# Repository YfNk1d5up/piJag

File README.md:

# piJag

Audio/Video Screen Unit of Jaguar X Type X400 based on a raspberry and openAuto pro: bluetooth, CarPlay, OBD, remote start, climate module control

[github] https://github.com/YfNk1d5up/piJag

## Hardware & Software

 - This project was initially thought for Jaguar X-Type X400 (2001) but some parts will work for other cars
 - It uses :
    - [Rpi 4B 4GB RAM](https://www.raspberrypi.com/products/raspberry-pi-4-model-b/)
    - [OpenAuto Pro](https://bluewavestudio.io/shop/openauto-pro-car-head-unit-solution/)
    - [CarPiHat](https://thepihut.com/products/carpihat-car-interface-hat-for-raspberry-pi)
    - [10.1" TouchScreen](https://www.amazon.fr/gp/product/B0B4VMNB42/ref=ppx_yo_dt_b_search_asin_image?ie=UTF8&psc=1)
    - [Carlinkit](https://www.amazon.fr/gp/product/B09ZQF182F/ref=ppx_yo_dt_b_asin_title_o05_s00?ie=UTF8&psc=1)
    - [USB Sound Card](https://www.amazon.fr/gp/product/B00IRVQ0F8/ref=ppx_yo_dt_b_asin_title_o04_s00?ie=UTF8&psc=1)
    - [Rear Camera](https://www.amazon.fr/gp/product/B0BG5M8H76/ref=ppx_yo_dt_b_asin_title_o01_s01?ie=UTF8&psc=1)
    - [CVBS to USB adapter](https://www.amazon.fr/gp/product/B0BYJ2892S/ref=ppx_yo_dt_b_asin_title_o01_s00?ie=UTF8&psc=1)
    - [12V Voltage Regulator](https://www.amazon.fr/gp/product/B09Q1XXM6G/ref=ppx_yo_dt_b_asin_title_o02_s00?ie=UTF8&psc=1)
    - [Powered USB Hub](https://www.amazon.fr/gp/product/B0BDFG1WZ7/ref=ppx_yo_dt_b_asin_title_o06_s00?ie=UTF8&psc=1)
    - [ELM327 OBD USB](https://www.amazon.fr/gp/product/B07NSPLVYW/ref=ppx_yo_dt_b_asin_title_o07_s00?ie=UTF8&psc=1)
    - 12V relays, Fan, Microphone, 4Channel Amplificator, HDMI & RCA cables, Audio Splitter ...
 - A custom PCB to control the Climate Control Module with an arduino nano (Kicad & JLCPCB)

## Features

- **Phone** : CarPlay, Android Auto, bluetooth, messages and calls
- **Rear Camera** : Automatic on reverse gear or anytime manually
- **Videos** : Kodi & Youtube
- **OBD** : CAN & SCP (Ford Protocol) messages and control
- **Climate** : Climate Control Module App
- **Mobile App** : Start the car, turn on heater or climatisation from Phone

## Screenshots

Setup not clean for now (you can see the Climate Control Module annoying me for now, explaination later)...

## Integration

### Raspberry Pi and carPiHat

The issue with installing custom hardware on a car is mainly how to power and connect them. Should I use the permanent 12V, switched 12V on key, interior lights 12V ...
The raspberry pi 4B is a 5V small computer that can draw 3A when loads are connected to it.
In this setup, a lot of usb devices are connected and I should consider this ~3A as a constant.
5V 3A, drawn from the car battery makes it impossible keeping powered on the constant battery supply.
In deed it needs to be powered off when I'm not in the car, and it needs a 12V to 5V step-down.
This is where I found [carPiHat](https://github.com/gecko242/CarPiHat) from TJD that saved me a lot of work :
- 12V - 5V buck converter to power the pi and touchscreen, with fuse and filtering.
- Safe shutdown circuitry to allow the pi to control its own power.
-  < 1mA current draw when switched off.
- Dedicated reverse, illumination and aux inputs, all opto isolated.
- 2 opto isolated general purpose inputs. (for a total of 5 inputs)
- 2 high current, high side switched 12V outputs (@1A). (for switching relays, lights ect)
- 1 independent CAN bus port.
- Real time clock to maintain system time across reboots.
- Broken out I2C bus.
- Broken out 1W for temperature sensor ect.
- 5V Power Output for display ect.

So the power aspect is done using this hat for the raspberry, connecting constant 12V, switched 12V, reverse gear input, illumination input, and GND

Then, a script makes the automation of the RPi power off 30s after turning the car off :

```python
import RPi.GPIO as GPIO # import our GPIO module
import time
from subprocess import call

GPIO.setmode(GPIO.BCM) # we are using BCM pin numbering

IGN_PIN = 12		# our 12V switched pin is BCM12
EN_POWER_PIN = 25	# our latch pin is BCM25

ILL_PIN = 13		# our 12V Illumination input pin is BCM13
REVERSE_PIN = 7	# our 12V Reverse Gear input pin is BCM7

IGN_LOW_TIME = 30 # time (s) before a shutdown is initiated after power loss

GPIO.setup(IGN_PIN, GPIO.IN) # set our 12V switched pin as an input
GPIO.setup(ILL_PIN, GPIO.IN) # same for ill and reverse 
GPIO.setup(REVERSE_PIN, GPIO.IN)

GPIO.setup(EN_POWER_PIN, GPIO.OUT, initial=GPIO.HIGH) # set our latch as an output

GPIO.output(EN_POWER_PIN, 1) # latch our power. We are now in charge of switching power off

ignLowCounter = 0

while 1:
	if GPIO.input(IGN_PIN) != 1: 				# if our 12V switched is not disabled
		time.sleep(1)							# wait a second
		ignLowCounter += 1						# increment our counter
		if ignLowCounter > IGN_LOW_TIME:		# if it has been switched off for >10s
			print("Shutting Down")
			call("sudo shutdown -h now", shell=True)	# tell the Pi to shut down
	else:
		ignLowCounter = 0 						# reset our counter, 12V switched is HIGH again

        time.sleep(0.1)  # Add a small sleep delay to reduce CPU usage
```

As said in TJD documentation in the *Opto-Isolated Inputs* section, I needed to redirect the CS1 pin to BCM24 to get ill and reverse inputs to work.

From the hat I also used the 2 outputs to control relays :
- One relay powers the **4Channels Audio Amplifier remote** and the rear camera with 12V
- The other powers the **36W USB Hub** to relieve the strain on the raspberry and charge devices.

(picture)

#### **Parts to come with carPiHat** :
- CAN integration
- I/O expander to add remote powering the car and other stuff

### TouchScreen 

Simply an HDMI and touch USB connected to the RPi, plus 5V power coming from the carPiHat

### Suffering from Hot Temperatures

During summer 2023, a lot of heat has made the setup suffer. This is where I add a 12V computer power fan to help keeping the whole setup at acceptable temperatures.

## obdSniffer

To add more control on the car, I tried to hack bus networks through the OBD2 port.

### CAN Bus

Following this awesome serie from Youtube [How to hack your car ](https://youtu.be/cAAzXM5vsi0) by Adam Varga and using his python&Qt [CAN_Gui](https://github.com/adamtheone/canDrive), I copy the setup to hack into my CAN Bus.

Here are for example some data I decoded : 

### SCP Bus

As the X-Type shares its creation with the Ford Mondeo, the car uses SAEJ1850 PWM aka **Standard Corporate Protocol** or **SCP** to communicate low priority information between modules.

A modification of Adam Varga code brings me the SCP decoding using the **ELM327 OBD2 USB Reader** using **AT** commands.
Modified functions :
*serialPacketReceiverCallback*
*serialPortConnect*
file *SerialReader.py*

(You can see some SCP data on the previous screenshot)

To achieve that, first I did some tests using AT on linux terminal

```bash
sudo screen /dev/ttyUSB0 38400
```

```bash
>atz
ELM327 v1.5

>atl1
OK

>ath1
OK

>ats1
OK

>atal
OK

>atsp1
OK

>atma

```

For AT commands explanation, SCP application case and another hardware setup, see this thread : https://www.jaguarforum.com/threads/reverse-engineering-hacking-scp-bus-to-xj-x350-x358-s-type-and-x-type.108639/

Example output :

```bash
81 29 60 02 0081 29 60 02 00 00 11
41 87 60 04 08 B1
81 7B 60 02 00 4C
81 7B 60 02 00 4C
```

See [X-Type Electrical Guide CAN/SCP](https://github.com/YfNk1d5up/piJag/blob/cf38571dc9505988becb3cf82d76548922db3a51/Docs/JagClimModule.pdf) to find more information about CAN and SCP messages

## OpenAuto Pro setup

## Climate Control Module Hack

The goal here was to remove the Control Unit that is space-consuming and overall avoid me to install the screen properly without destroying the case.
To continue adding a modern touch to my X-Type, I enjoy controlling the climate directly on the touchscreen via an app on openAuto Pro.

Firstly, I need to understand well how the existing module works.
So I bought another one to avoid getting stuck breaking it : in deed, it is connected to the CAN Bus and the car will not start if the module doesn't work or isn't connected to the bus.

By the CAN and SCP analyse done previously, I found that buttons user actions are not going through any bus on the car, plus the electrical documentation shows that the module only communicate with other modules to say an action has been performed.
FYI, the second X-Type (X404) added LIN to the buses, where climate, windows control, driver wheel buttons, etc, communicate through it.

But no chance, that is not the case for my version. So sending commands on buses to control the climate module is impossible.

That said, there is no other way than hacking electronics of the module by adding a custom Mod PCB.

The Module consists in 2 PCBs connected by a 20 wires ribbon. On the electrical documentation, only the global module connections to the rest of the car is detailed. 
Lucky for me, somebody already took a look into that module, because he wanted to change the screen to a modern one. The report is joined in [David's initial HVAC Sniffer](https://github.com/YfNk1d5up/piJag/blob/cf38571dc9505988becb3cf82d76548922db3a51/Docs/p10018_jag_hvac_sniffer.zip)

The first PCB contains the MCU which does CAN communication to the rest of the vehicule, control of fans, compressor, etc : that is the one I want to keep.
The second one contains all the buttons, the LCD screen, a digital encoder, and maybe a second propietary MCU impossible to identify : I want to replace this PCB.
Doing some retro-engineering and finding the documentation of the MCU in the first PCB, here is the connection from and to that second PCB :

[Initial retro-engineering of the 2nd PCB](https://github.com/YfNk1d5up/piJag/blob/cf38571dc9505988becb3cf82d76548922db3a51/Docs/piJagClim_existing_module.pdf)

You can see here a switches matrix, using 6 wires for 12 buttons. An I2C screen connected straigth to the main MCU, a rotary encoder also directly connected to the main board.
What I used for the buttons is analog switches, that works as relays except that they are small 14 pins chips, which each entry is controlled by an Arduino digital pin. For the rotary encoder, an Arduino Nano can easily simulate the signals by using two digital pins.
Finally, using David's work about the i2c screen, I can get the information coming from the main MCU by decoding it using A4 and A5 pins on the Nano.

And so here is the mod board :

JLCPCB Manufacture :

![PCB not mounted]
![PCB mounted]

To communicate with the arduino onboard, a pyQt App controls the mod, associated with an arduino code that simulates the action and transmit the i2c data.

[pyQtApp](Software/piJagClimApp)
[piJagClimI2C.ino](Hardware/piJagClim/newPCB/arduino/piJagClimI2C/piJagClimI2C.ino)

Here you can see the Qt App v0.1 :

## Ressources

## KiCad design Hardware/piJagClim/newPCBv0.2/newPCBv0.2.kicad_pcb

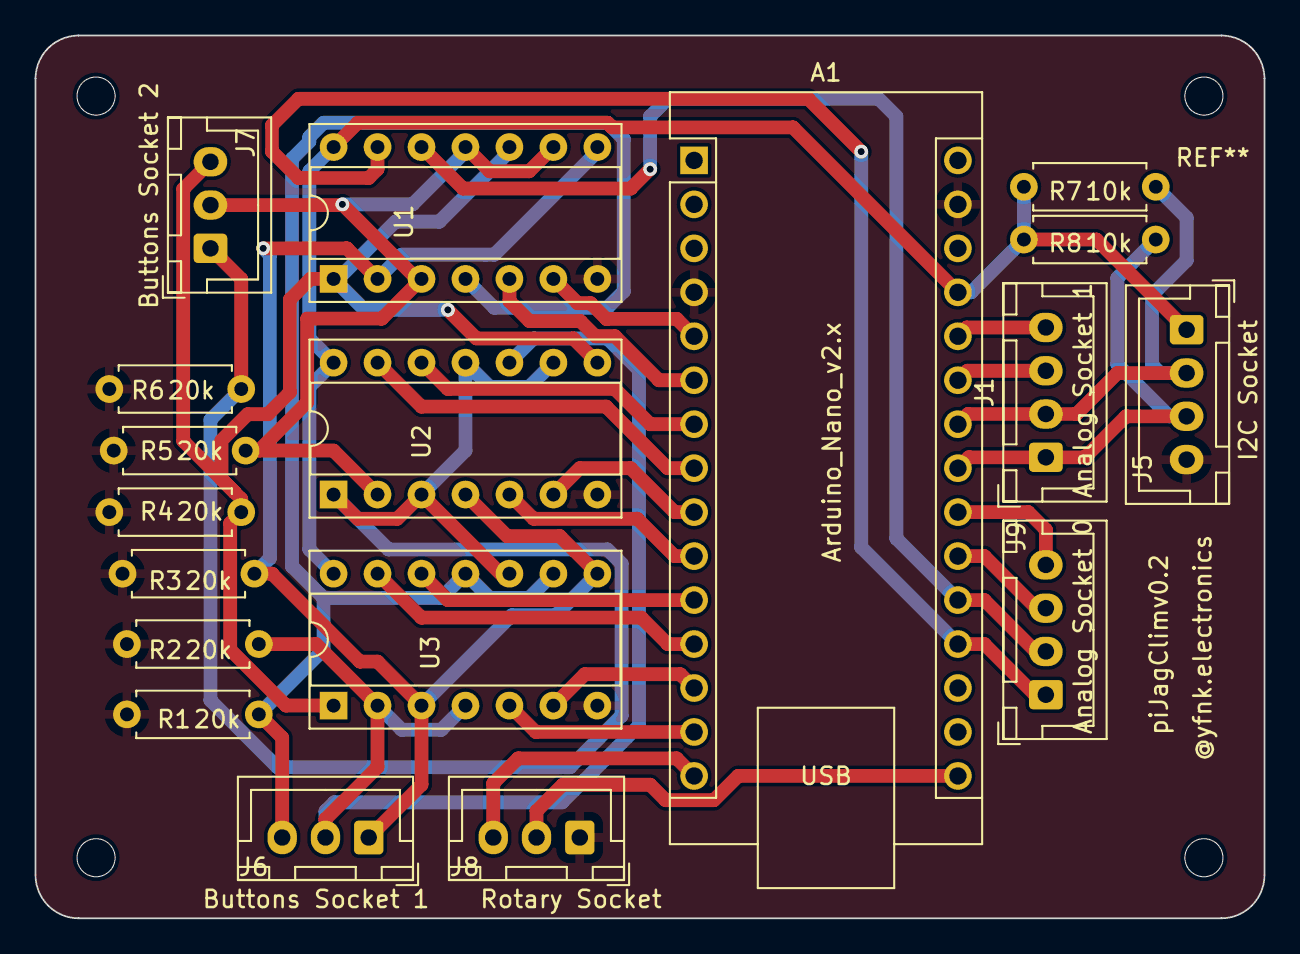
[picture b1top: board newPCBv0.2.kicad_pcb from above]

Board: 2 copper layers, 71.0 x 51.0 mm, 18 parts (0 on the bottom side), 28 nets.

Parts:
A1: Arduino_Nano_v2.x; Arduino_Nano
J1: Analog Socket 1; JST_XH_B4B-XH-A_1x04_P2.50mm_Vertical
J5: I2C Socket; JST_XH_B4B-XH-A_1x04_P2.50mm_Vertical
J6: Buttons Socket 1; JST_XH_B3B-XH-A_1x03_P2.50mm_Vertical
J7: Buttons Socket 2; JST_XH_B3B-XH-A_1x03_P2.50mm_Vertical
J8: Rotary Socket; JST_XH_B3B-XH-A_1x03_P2.50mm_Vertical
J9: Analog Socket 0; JST_XH_B4B-XH-A_1x04_P2.50mm_Vertical
R1, R2, R3, R4, R5, R6: 20k; R_Axial_DIN0207_L6.3mm_D2.5mm_P7.62mm_Horizontal
R7, R8: 10k; R_Axial_DIN0207_L6.3mm_D2.5mm_P7.62mm_Horizontal
U1, U2, U3: DIP-14_W7.62mm_Socket

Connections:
2: A1.16 (D13), J8.2
3: J7.1, R6.1, U2.1 (in/out_A), U2.3 (in/out_B), U2.9 (in/out_C), U2.11 (in/out_D), U3.10 (in/out_D)
4: J7.2, R5.1, U1.3 (in/out_B), U1.9 (in/out_C), U1.11 (in/out_D), U2.2 (in/out_A)
5: J7.3, R4.1, U1.1 (in/out_A), U1.10 (in/out_D), U2.8 (in/out_C), U3.1 (in/out_A)
8: A1.24 (A5), J1.2, J5.2, R7.2
11: A1.4 (GND), A1.29 (GND), J5.4, J8.1, R1.2, R2.2, R3.2, R4.2, R5.2, R6.2, U1.7 (Vss), U2.7 (Vss), U3.7 (Vss)
13: A1.23 (A4), J1.1, J5.3, R8.2
14: A1.27 (+5V), J5.1, R7.1, R8.1, U1.14 (Vdd), U2.14 (Vdd), U3.14 (Vdd)
17: J6.1, R3.1, U1.2 (in/out_A), U1.8 (in/out_C), U2.4 (in/out_B), U3.3 (in/out_B), U3.8 (in/out_C)
18: J6.2, R2.1, U2.10 (in/out_D), U3.2 (in/out_A), U3.4 (in/out_B)
19: J6.3, R1.1, U1.4 (in/out_B), U3.9 (in/out_C), U3.11 (in/out_D)
20: A1.15 (D12), J8.3
A: A1.19 (A0), J9.1, U1.13 (Control_A)
A': A1.8 (D5), U2.13 (Control_A)
A'': A1.12 (D9), U3.13 (Control_A)
B: A1.6 (D3), U1.5 (Control_B)
B': A1.10 (D7), U2.5 (Control_B)
B'': A1.14 (D11), U3.5 (Control_B)
C: A1.5 (D2), U1.6 (Control_C)
C': A1.9 (D6), U2.6 (Control_C)
C'': A1.13 (D10), U3.6 (Control_C)
D: A1.20 (A1), J9.2, U1.12 (Control_D)
D': A1.7 (D4), U2.12 (Control_D)
D'': A1.11 (D8), U3.12 (Control_D)
unnamed: A1.21 (A2), J9.3
unnamed: A1.22 (A3), J9.4
unnamed: A1.25 (A6), J1.3
unnamed: A1.26 (A7), J1.4

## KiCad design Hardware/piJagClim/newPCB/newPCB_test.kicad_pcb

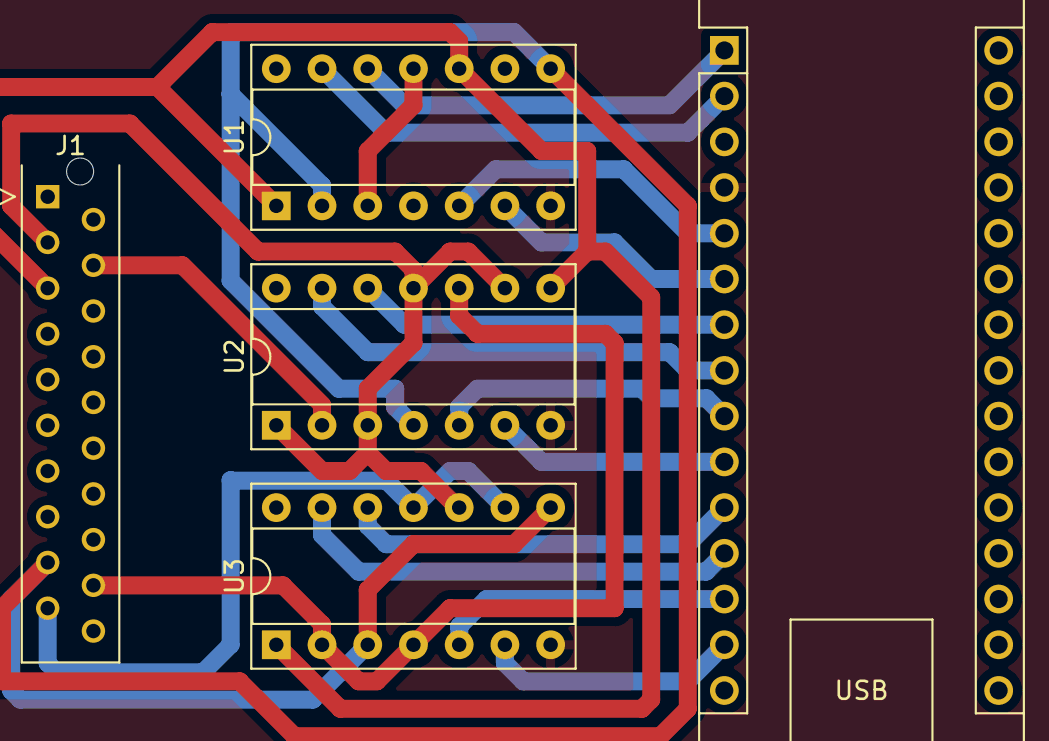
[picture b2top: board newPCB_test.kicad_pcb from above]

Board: 2 copper layers, 5 parts (0 on the bottom side), 20 nets.

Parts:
A1: Arduino_Nano_v2.x; Arduino_Nano
J1: Grey_Ribbon_Main_PCB; TE_Micro-MaTch_2-215079-0_2x10_P1.27mm_Vertical
U1, U2, U3: DIP-14_W7.62mm_Socket

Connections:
3: J1.3, U2.1 (in/out_A), U2.3 (in/out_B), U2.9 (in/out_C), U2.11 (in/out_D), U3.10 (in/out_D)
4: J1.4, U1.3 (in/out_B), U1.9 (in/out_C), U1.11 (in/out_D), U2.2 (in/out_A)
5: J1.5, U1.1 (in/out_A), U1.10 (in/out_D), U2.8 (in/out_C), U3.1 (in/out_A)
17: J1.17, U1.2 (in/out_A), U1.8 (in/out_C), U2.4 (in/out_B), U3.3 (in/out_B), U3.8 (in/out_C)
18: J1.18, U2.10 (in/out_D), U3.2 (in/out_A), U3.4 (in/out_B)
19: J1.19, U1.4 (in/out_B), U3.9 (in/out_C), U3.11 (in/out_D)
+5V: A1.27 (+5V), U1.14 (Vdd), U2.14 (Vdd), U3.14 (Vdd)
A: A1.2 (D0/RX), U1.13 (Control_A)
A': A1.8 (D5), U2.13 (Control_A)
A'': A1.12 (D9), U3.13 (Control_A)
B: A1.5 (D2), U1.5 (Control_B)
B': A1.9 (D6), U2.5 (Control_B)
B'': A1.13 (D10), U3.5 (Control_B)
C: A1.6 (D3), U1.6 (Control_C)
C': A1.10 (D7), U2.6 (Control_C)
C'': A1.14 (D11), U3.6 (Control_C)
D: A1.1 (D1/TX), U1.12 (Control_D)
D': A1.7 (D4), U2.12 (Control_D)
D'': A1.11 (D8), U3.12 (Control_D)
GND: A1.4 (GND), U1.7 (Vss), U2.7 (Vss), U3.7 (Vss)

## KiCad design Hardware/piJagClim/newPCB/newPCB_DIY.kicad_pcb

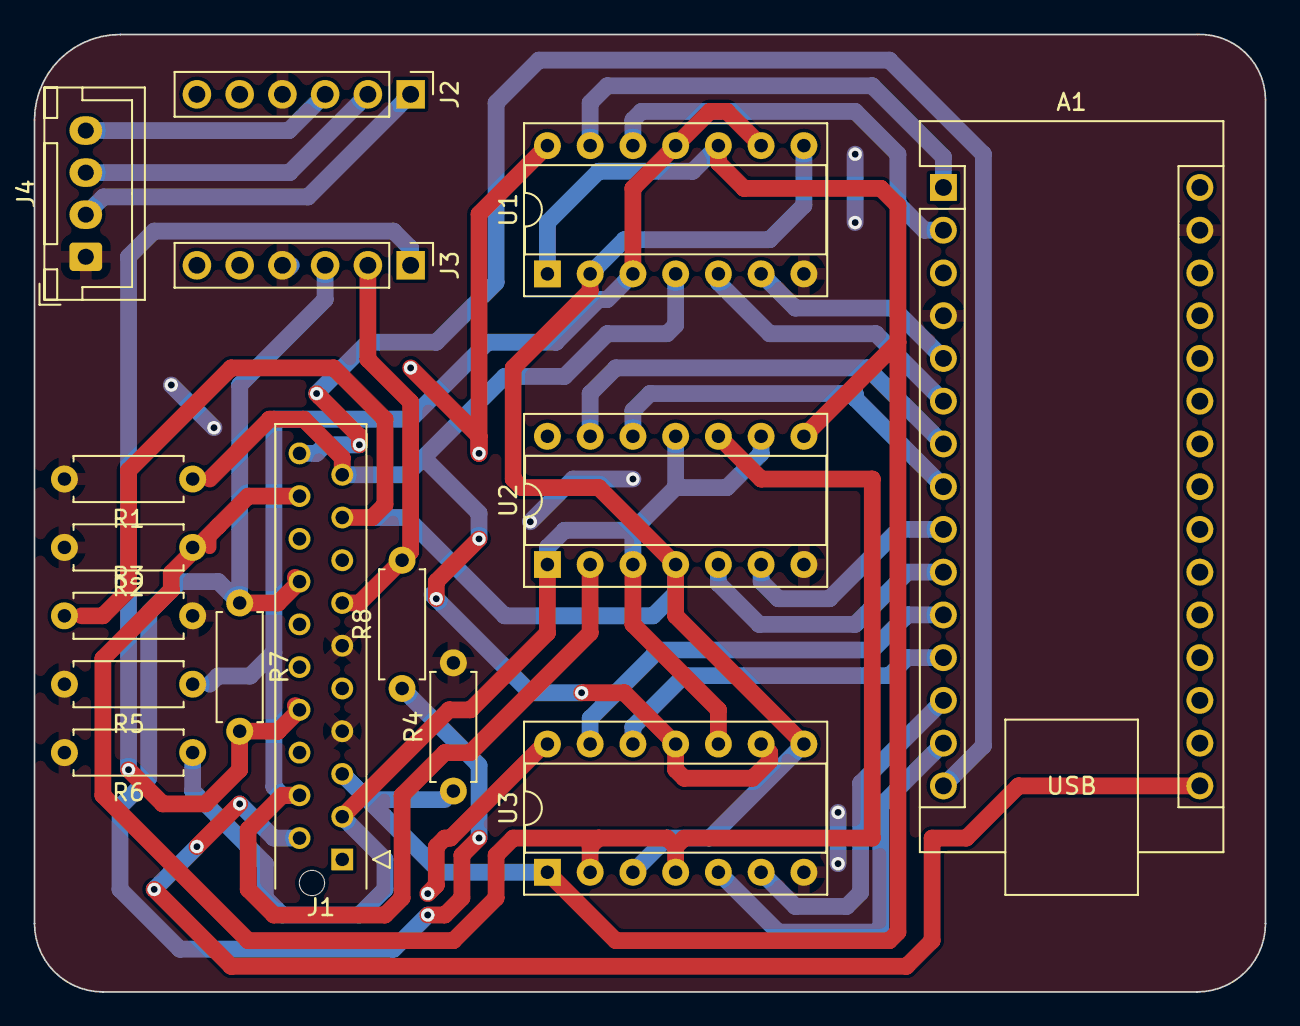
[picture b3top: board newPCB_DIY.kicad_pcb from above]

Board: 2 copper layers, 73.2 x 56.9 mm, 16 parts (0 on the bottom side), 28 nets.

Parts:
A1: Arduino_Nano_v2.x; Arduino_Nano
J1: Grey_Ribbon_Main_PCB; TE_Micro-MaTch_2-215079-0_2x10_P1.27mm_Vertical
J2, J3: Conn_01x04_Pin; PinHeader_1x06_P2.54mm_Vertical
J4: Conn_01x04_Pin; JST_XH_B4B-XH-A_1x04_P2.50mm_Vertical
R1, R2, R3, R4, R5, R6: 20k; R_Axial_DIN0207_L6.3mm_D2.5mm_P7.62mm_Horizontal
R7, R8: 10k; R_Axial_DIN0207_L6.3mm_D2.5mm_P7.62mm_Horizontal
U1, U2, U3: DIP-14_W7.62mm_Socket

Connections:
2: A1.16 (D13), J1.2
3: J1.3, R6.1, U2.1 (in/out_A), U2.3 (in/out_B), U2.9 (in/out_C), U2.11 (in/out_D), U3.10 (in/out_D)
3V3: J2.3, J4.4
4: J1.4, R5.1, U1.3 (in/out_B), U1.9 (in/out_C), U1.11 (in/out_D), U2.2 (in/out_A)
5: J1.5, R4.1, U1.1 (in/out_A), U1.10 (in/out_D), U2.8 (in/out_C), U3.1 (in/out_A)
8: J1.8, J3.1, R7.2
11: A1.4 (GND), A1.29 (GND), J1.7, J1.11, J2.4, J3.4, J4.1, R1.2, R2.2, R3.2, R4.2, R5.2, R6.2, U1.7 (Vss), U2.7 (Vss), U3.7 (Vss)
13: J1.13, J3.2, R8.2
14: J1.14, J3.3, R7.1, R8.1
17: J1.17, R3.1, U1.2 (in/out_A), U1.8 (in/out_C), U2.4 (in/out_B), U3.3 (in/out_B), U3.8 (in/out_C)
18: J1.18, R2.1, U2.10 (in/out_D), U3.2 (in/out_A), U3.4 (in/out_B)
19: J1.19, R1.1, U1.4 (in/out_B), U3.9 (in/out_C), U3.11 (in/out_D)
20: A1.15 (D12), J1.20
+5V: A1.27 (+5V), U1.14 (Vdd), U2.14 (Vdd), U3.14 (Vdd)
A: A1.1 (D1/TX), U1.13 (Control_A)
A': A1.7 (D4), U2.13 (Control_A)
A'': A1.11 (D8), U3.13 (Control_A)
B: A1.6 (D3), U1.5 (Control_B)
B': A1.10 (D7), U2.5 (Control_B)
B'': A1.14 (D11), U3.5 (Control_B)
C: A1.5 (D2), U1.6 (Control_C)
C': A1.9 (D6), U2.6 (Control_C)
C'': A1.13 (D10), U3.6 (Control_C)
D: A1.2 (D0/RX), U1.12 (Control_D)
D': A1.8 (D5), U2.12 (Control_D)
D'': A1.12 (D9), U3.12 (Control_D)
SCL2: J2.1, J4.2
SDA2: J2.2, J4.3

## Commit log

2023-07-16 first global commit
2023-07-16 pictures
2023-07-16 obdSniffer pictures
2023-07-16 Readme
2023-07-17 HVAC photo
2023-07-17 BUS Networks screenshot
2023-07-17 Docs
2023-07-17 modPCB
2023-07-17 wiringSetup
2023-07-17 new photos
2023-09-01 arduino test new PCB
2023-09-03 I2C & control + - of climate module test
2023-09-03 git test
2023-09-03 new pcb piJagClim version
2023-09-03 serial com python-arduino test
2023-09-04 Reading temperature
2023-09-05 All readings and controls except Fan
2023-09-05 Qt first version
2023-09-05 rotary encoder
2023-09-05 removed delay 100ms
2023-09-06 GUI with almost all functions
2023-09-06 removed pycache
2023-09-06 test custom Dial
2023-09-06 Add support to python <3.10
2023-09-06 Threads for receiving and sending through serial
2023-09-06 Command to send data when asked
2023-09-06 More photos
2023-09-06 photos not in right dir
2023-09-06 Replaced PCB v0.2 and Added pyQT App
2023-09-07 Color change on custom QDials
2023-09-07 UI Backup
2023-09-07 removed __pycache__
2023-09-07 Gradient on custom Dial
2023-09-07 Global window layout & Knobs design & On Off Button
2023-09-07 pycache
2023-09-07 Changed delays
2023-09-08 directory structures and val on dial
2023-09-08 Design Auto on knob and working on adding value
2023-09-08 Background on pushButtons
2023-09-08 Control buttons design
2023-09-08 Screenshot piJagClimAppv0.11
2023-09-08 Update Picture
2023-09-09 Final UI v0.11
2023-09-09 Bash Script
2023-09-09 clim App v0.12
2023-09-09 piJagClimApp v0.12
2023-09-16 USB port fixed and rules file
2023-09-16 App sh for OpenAutoPro
2023-09-16 App Icon
2023-09-16 Maximized window and working relative path
2023-09-16 new icon
2023-09-19 Initialize v0.2 piJagClimGui
2023-09-20 working on gui design
